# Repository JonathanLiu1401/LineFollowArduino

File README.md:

# UW EE201: Autonomous Line Following Robot

🏆 **All-Time Record Holder:** This robot achieved the all-time fastest track record of **24.5 seconds** in the University of Washington EE201 Line Following Car Competition, securing first place by a margin of over 6 seconds.

This repository contains the complete hardware, mechanical, and software design files for our group's autonomous line-following robot. The system features a custom 3D printed chassis, a bespoke sensor array PCB, and an advanced Arduino-based closed-loop PID control system optimized for aggressive cornering and high-speed straightaways.

## Performance Demonstration

**Record-Breaking 24.5s Run:**
<video src="20260305_180107.mp4" controls="controls" style="max-width: 100%;">
  Your browser does not support the video tag.
</video>

**Robot Overview:**

## Repository Structure

Based on the root directory, the project files are organized as follows:

* **`ee201_final_project_sensor_array/`**
  Contains the schematic and board layout files for the custom 7-sensor Light Dependent Resistor (LDR) analog front-end and tuning interface.
* **`EE201_group6_chassis.stl`**
  The 3D CAD file for the custom-designed robot chassis, optimized for a low center of gravity and precise sensor-to-ground focal distance.
* **`final_line_follower.ino`**
  The final, competition-winning firmware featuring time-based dynamic throttling and quadratic error scaling.
* **`10_5_line_follower_code.ino`**
  A legacy development iteration of the line following logic.

## Hardware Architecture

### Electronics and PCB Design
The electrical system is driven by an Arduino Mega interfaced with an Adafruit Motor Shield V2. A custom PCB was engineered to streamline the analog front-end.
* **Sensor Array:** Seven LDRs configured in voltage divider circuits, spaced precisely to capture standard competition line widths.
* **Control Interface:** Four onboard potentiometers routed to analog pins (A0 through A3) allow for live parameter tuning of Speed, Proportional, Integral, and Derivative gains without requiring firmware recompilation.

### Mechanical Design
The mechanical chassis was manufactured via 3D printing to house the hardware securely. 
* It securely mounts the DC motors, battery payload, and microcontroller stack to prevent center-of-gravity shifts during high-speed cornering. 
* It integrates the sensor mount to keep the LDR PCB at a fixed, optimal distance from the track surface to maximize the black-to-white contrast ratio.

## Software Architecture

The primary firmware (`final_line_follower.ino`) is built in C++ and implements an advanced kinematic control loop. To achieve the record-breaking 24.5 second time, several major algorithmic optimizations were implemented to completely replace the baseline starter code logic.

### Algorithmic Advancements

* **Temporal Dynamic Throttling:** The baseline code utilized a static speed output. The winning firmware implements a clock-driven control state that tracks execution time using the hardware `millis()` timer. Between 8.5 seconds and 17.5 seconds into the run, the algorithm mathematically divides the user-defined speed boost by a factor of 2.3. This ensures the robot maintains absolute maximum velocity on the starting and ending straightaways while automatically decelerating to navigate the dense stacked-turn section with maximum grip.
* **Quadratic Proportional Gain:** The original PID implementation calculated the proportional turning force linearly. The updated control loop scales the proportional error quadratically. By multiplying the error by its absolute ratio over the maximum possible error, the algorithm heavily attenuates steering corrections near the center line. This eliminates high-speed straight-line wobbling while retaining 100 percent control authority at the extreme sensor edges for 90-degree pivots.
* **Exponential Moving Average (EMA) Derivative Filter:** The original raw discrete derivative calculation was highly susceptible to analog sensor noise, causing jitter. The modified code passes the raw derivative through an EMA low-pass filter with a smoothing factor of 0.4. This prevents erratic micro-corrections and allows the system to support a significantly higher derivative gain (kD = 170) to dampen overshoots during aggressive cornering.
* **Asynchronous Hardware Polling:** The starter code executed analog-to-digital conversions to read all four potentiometers during every loop iteration. The winning code introduces a modulo counter to restrict potentiometer polling to once every 5000 loop cycles. This dramatically reduces loop execution time, allowing the microcontroller to sample the photoresistors and update the motor PWM outputs at a much higher frequency. 
* **Rapid Static-State Calibration:** The original calibration sequence utilized synchronous LED blinking (`delay()` based logic) to indicate sampling progress, which artificially bottlenecked the processor and dragged the 40-sample process out to over 20 seconds. We stripped out the blocking blink logic and replaced it with a static LED indicator. This optimization slashed the total calibration time down to just 5 seconds, vastly improving pre-race setup efficiency without sacrificing sensor accuracy.
* **Hardware Safety Interlocks:** A dedicated safety algorithm continuously monitors the raw sensor array data to detect abnormal environmental states. If the system detects all darkness (indicating the robot has been lifted or driven off a table) or all white (indicating total line loss), it circumvents the PID calculation and instantly cuts power to the drive motors to prevent runaway hardware damage.

## Setup and Calibration

1. **Hardware Assembly:** Mount the Arduino, Motor Shield, and DC motors to the 3D printed chassis. Connect the custom PCB to the analog header block.
2. **Firmware Upload:** Flash `final_line_follower.ino` to the Arduino Mega.
3. **Calibration Sequence:**
    * Power the robot on while placing the sensor array strictly over the **white** surface.
    * Wait for the onboard LED indicator to turn on, signaling active white calibration.
    * Move the robot so the sensor array is directly over the **black** line during the 1-second delay window.
    * The robot will complete the black calibration, start the internal race clock, and immediately engage the motors.

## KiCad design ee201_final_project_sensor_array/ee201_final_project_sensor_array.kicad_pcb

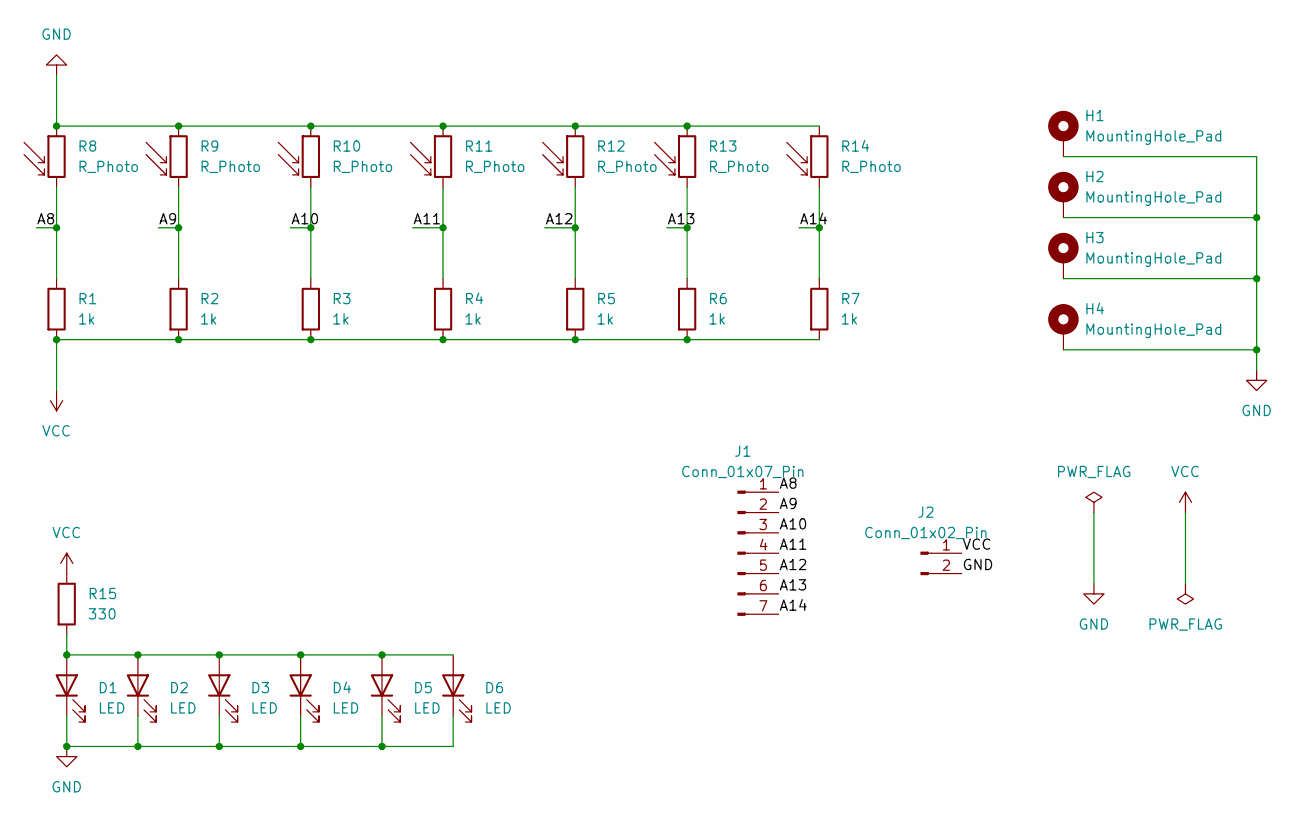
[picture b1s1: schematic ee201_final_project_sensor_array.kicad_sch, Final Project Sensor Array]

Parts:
D1, D2, D3, D4, D5, D6: LED; LED_D5.0mm
H1, H2, H3, H4: MountingHole_Pad; MountingHole_3.2mm_M3_Pad
J1: Conn_01x07_Pin; PinHeader_1x07_P2.54mm_Vertical
J2: Conn_01x02_Pin; PinHeader_1x02_P2.54mm_Vertical
R1, R2, R3, R4, R5, R6, R7: 1k; R_Axial_DIN0207_L6.3mm_D2.5mm_P10.16mm_Horizontal
R8, R9, R10, R11, R12, R13, R14: R_Photo; R_LDR_5.0x4.1mm_P3mm_Vertical
R15: 330; R_Axial_DIN0207_L6.3mm_D2.5mm_P10.16mm_Horizontal

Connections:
/A8: J1.1, R1.1, R8.2
/A9: J1.2, R2.1, R9.2
/A10: J1.3, R3.1, R10.2
/A11: J1.4, R4.1, R11.2
/A12: J1.5, R5.1, R12.2
/A13: J1.6, R6.1, R13.2
/A14: J1.7, R7.1, R14.2
GND: D1.1 (K), D2.1 (K), D3.1 (K), D4.1 (K), D5.1 (K), D6.1 (K), H1.1, H2.1, H3.1, H4.1, J2.2, R8.1, R9.1, R10.1, R11.1, R12.1, R13.1, R14.1
unnamed: D1.2 (A), D2.2 (A), D3.2 (A), D4.2 (A), D5.2 (A), D6.2 (A), R15.2
VCC: J2.1, R1.2, R2.2, R3.2, R4.2, R5.2, R6.2, R7.2, R15.1

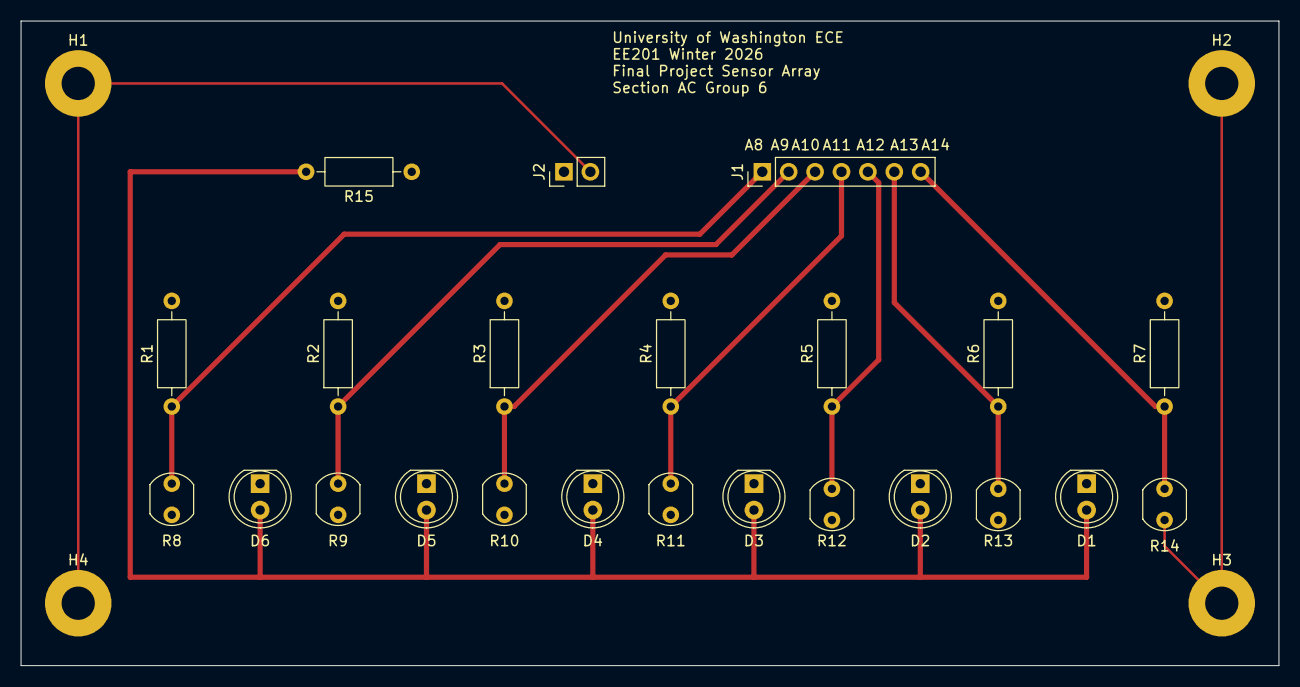
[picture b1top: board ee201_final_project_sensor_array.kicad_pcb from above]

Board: 2 copper layers, 121.0 x 62.0 mm, 27 parts (0 on the bottom side), 10 nets.

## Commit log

2026-03-02 added quadratic error scaling
    quadratic error scaling to reduce oscillations on straight paths
2026-03-02 Add files via upload
    added quadratic error scaling for kdrop to reduce speed reductions on straight paths
2026-03-03 speed penalty removed
    stable (i think)
2026-03-03 bug fixes
2026-03-06 24.5 seconds
    Final line follower able to complete UW line following car track in under 24.5s with fully charged battery and high P and D values (~100). Changes include hard coded speed up and slow down sections, 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
2026-03-14 Sensor Array PCB Design
    Designed in KiCAD
2026-03-14 Chassis
    Chassis stl for 3d print
2026-03-14 Initialize README with project overview and setup
    Added detailed documentation for the autonomous line-following robot project, including hardware, software, and calibration instructions.
2026-03-14 Refine README content and formatting
    Updated README to improve clarity and formatting.
2026-03-14 clarifications
2026-03-14 Add performance demonstration section to README
